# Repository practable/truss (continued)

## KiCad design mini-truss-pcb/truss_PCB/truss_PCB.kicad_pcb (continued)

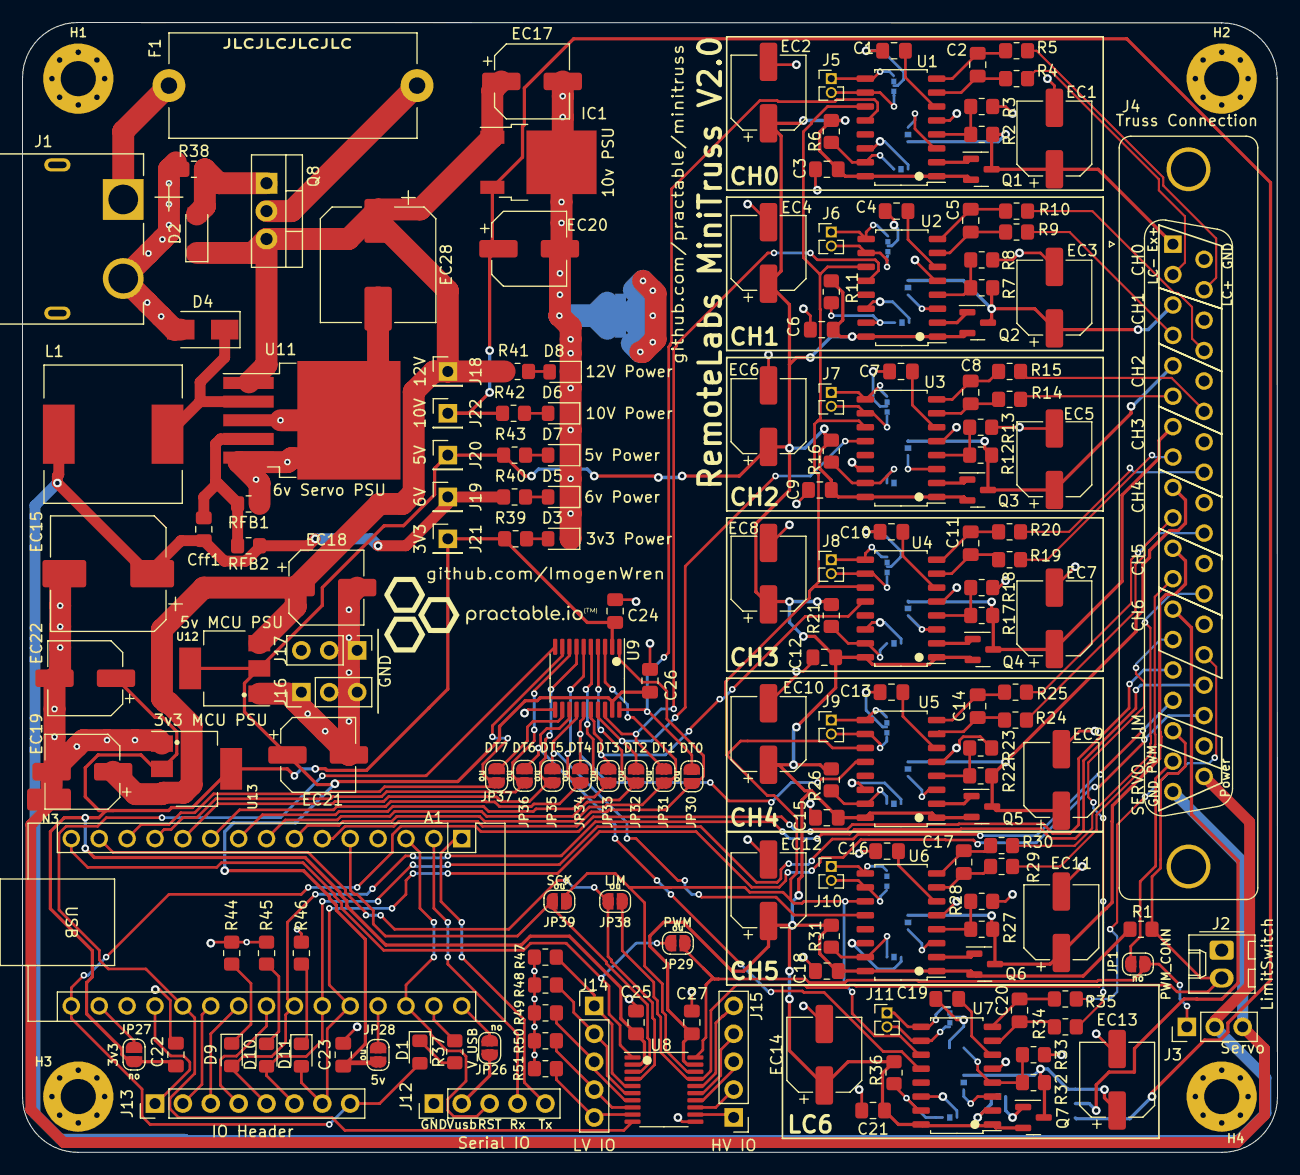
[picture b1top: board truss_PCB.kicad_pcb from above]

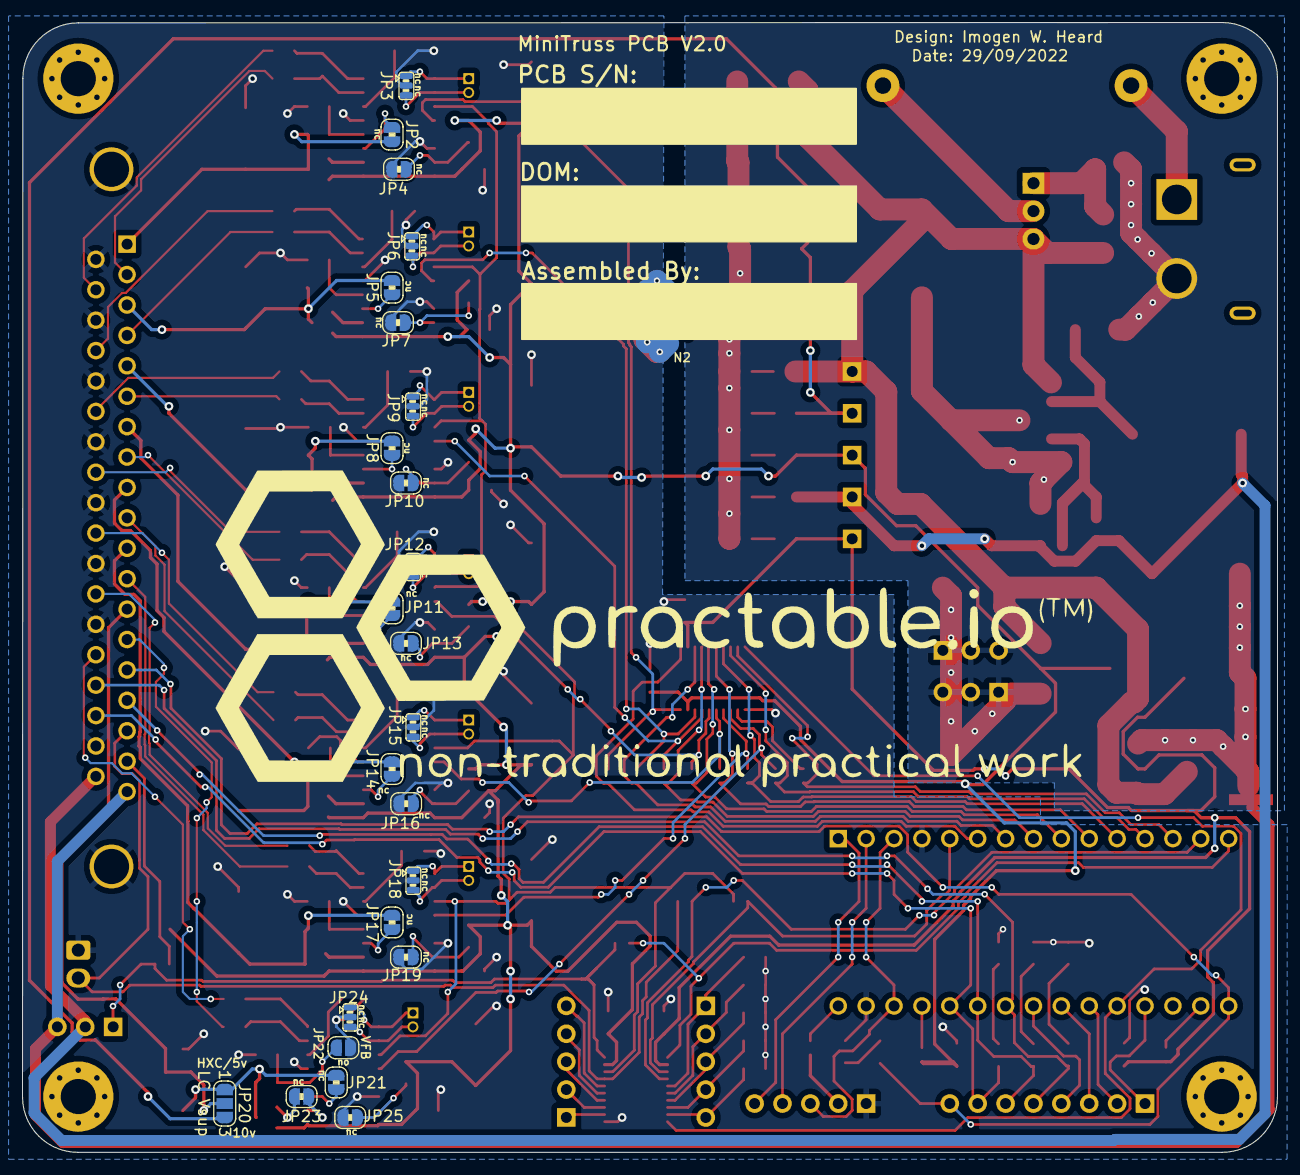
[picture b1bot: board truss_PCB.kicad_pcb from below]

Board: 2 copper layers, 114.3 x 102.9 mm, 205 parts (25 on the bottom side), 157 nets.

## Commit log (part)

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2022-08-30 readme update
2022-08-30 ui and fw files added and readme updated
2022-08-30 removed dist folder from ui
2022-08-30 physically deleted dist folder
2022-08-30 Create LICENSE
2022-09-01 updated hard limit switch state
2022-09-01 removed interrupt for testing
2022-09-01 minor change to limit variable names
2022-09-02 updated servo library to better reach 0 point -> 0 position not exactly 1ms pulse
2022-09-02 changed limit switch functionality to just jump into ZERO state if limit hit
2022-09-02 limit state functional, sets flag, flag runs zero mode, zeroing returns flag to false
2022-09-02 hard limit state removed
2022-09-05 delay changed to constant value after high pulse
2022-09-05 updated scale factors from int to float
2022-09-05 updated gauge factors from int to float
2022-09-06 Add odroid setup
2022-09-06 sbc: fix apt, install python
2022-09-06 sbc: fix ffmpeg install
2022-09-06 sbc: fix install-firmware playbook
2022-09-06 sbc: add prepare
2022-09-12 sbc: add mo to installation instructions
2022-09-12 sbc: improve instruction in README
2022-09-12 sbc: Fix commands in README
2022-09-13 initial commit with new FlashStorage library
2022-09-13 have added secure cal states and functions to truss firmware. Needs testing.
2022-09-15 sbc: fix shellhost install task
2022-09-15 sbc: fix token selection
2022-09-16 merged update to main
2022-09-16 have completed secure cal setting and integration with truss firmware
2022-09-23 updated load cal and can get loaded cal
2022-09-23 added calibration data for 8 trusses
2022-09-26 sbc: update README for manual token change
2022-09-27 updated reset to run on firmware startup and for UI reset to be setting 0 position
2022-09-27 updated reset on startup on firmware
2022-09-29 update to theoretical strains for new truss dimensions
2022-09-29 calibration data updated
2022-09-29 truss image updated
2022-09-30 minor updates to popup help text
2022-09-30 sbc: add powerbutton script
2022-09-30 sbc: fix powerbutton script
2022-09-30 sbc: add powerbutton service
2022-10-03 calibration data added for trus05
2022-10-04 truss image has blurred out number so as not to confuse students
2022-10-06 added ability to set STARTUP state from serial, allowing recalibration without power cycle
2022-10-07 removed old calibration data
2022-10-07 update to readme
2022-10-07 increased number of writes possible to flashstorage
2023-03-06 migration to vite
2023-03-06 tests migrated to vitest
2023-03-06 id on popups removed according to eslint
2023-03-06 updates for open day made, need to test
2023-03-07 updated snapshot to display only integer values
2023-03-07 updated title from truss1.0 to truss
2023-03-07 base path update for open day
2023-04-25 slight update to tests, need to correct some issues on move from jest to vitest
2023-04-25 added new image including force arrow
2023-04-25 new folder structure for multiple UIs
2023-04-25 updated readme for separate UIs
2023-04-25 updated readme and added vitest run to open-day UI
2023-04-25 update to README to explain how to make updates to UI versions
2023-06-06 Added all files for mini-truss-pcb
    #Note: Github link on the PCB says /minitruss but it felt better having that PCB design just part of this repo. Would it break anything to rename this minitruss at somepoint, or should I create a new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
2023-06-06 Added the correct mini truss pcb folder
2023-06-20 added basic firmware tests
2024-09-23 ui/no-force-1.0 (update): remove console logging on no-force ui and update base path
2025-07-25 reorganised secret functions into new tab without changing any functionality
2025-08-11 updated kicad repos
2025-08-20 truss/hw (fix): add cad files and additional documentation for hardware.
2025-09-02 ui (fix): update all UIs to use env variables for base path and add version to information popup
2025-09-02 ui/default (v2.0.0): update to v2.0.0 - new css style, practable component class added, ids added to all interactive components for logging, layout updates, UUID storage and display added, removed le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
2025-09-02 ui/open-day (new): add v2 of open day ui, but keep v1 in open-day-v1
2025-09-02 ui/README.md (add): add readme of ui variants and version details
2025-09-03 ui/no-force-v2 (add): add v2 of the sm2 no-force ui for truss
2025-09-11 ui/default (fix): add tick marks on menu items
2025-09-11 ui/no-force and ui/open-day (fix): add tick marks to menu items
2026-01-22 ui/no-force (fix): add graph nodes to the logging-config
